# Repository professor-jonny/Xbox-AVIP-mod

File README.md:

# Xbox Avip mod

## Project Info
We all know that modern TV's are going away from component and composite video inputs in favor of newer technologies such as HDMI because of this there has been many people attempting various mods some great, some sketchy and some down right wrong.

This project started as I have seen a few people damage their Xbox consoles by attempting VGA and HDMI mods or made such a bad job of it that that I decided something needed to be done and I set out to make up a basic QSB to break out signals that you can use within the console to attached to external connectors or for use with an internal video adaptor solution.
Design goals were to be simple quick to install and have no complicated binary logic external switches to select the video modes.

The design also includes a buffer circuit to drive the internal h and v sync signals to 5v to give you proper VGA compliant signals with a suitable bios.

The system includes a PICAXE microcontroller to be able to switch video modes and other trickery, I designed it using this over a traditional microcontroller for ease of a user to modify using a three wire serial connection (in circuit) and partly from my lack of programming skills and time.
The PICAXE system enables any one to reprogram it without too much hassle and with minimal programming knowledge, both flow chart and basic programs are provided as samples that are easy to follow and understand.

I have also designed some breakout boards to join to the AVIP mod board, or you could use get IPEX/ U.FL to solder tails to connect to some sort of internal adaptor or converter in my perisomal Xbox I milled pads to place IPEX/ U.FL sockets on a component to HDMI adaptor.

I had double ended U.FL /IPEX Connectors made for this project officially the connectors are actually 50 ohm but were made with 75 ohm cable so the impedances are not perfect but it was the only aspect of the project I was not happy with, I planned to further update this project with a flex or FFC cable between boards but I'm unsure on impedance matching and the design of such a cable if someone can offer us some help with that I would be very grateful.

I realize at 720p the bandwidth can tip 75MHZ so the cable will need to be designed with microstrip or stripline transmission mitred bends or as such but I don't know much about the property's of these FFC cables or FlexPCB's or their connectors.

## Rational over other mods
I realize that there are other mods that offer better solutions or something of a similar goal such as native digital output or internal component to HDMI etc... but many are not simple or cost effective.
Many require de-soldering the original AVIP connector or micro soldering and for many people this is something that is beyond their skill set but a QSB solution is very noob friendly and hence my project.

## Features
The AVIP  mod has the following features:
  * Pluggable RF connectors for AV signals.
  * Impedance matched shielded analogue signals.
  * Automatic selection of backup AV mode.
  * VGA compliant 5V buffered V and H sync signals (non inverted).
  * Video mode toggling.
  * Fits all motherboard revisions.
  * Additional optional audio and video breakout boards.
  * Open source design.
  * In circuit user reprogrammable.
  * Audible/ light mode indication options.
  * Expansion capabilities.
  * AV pack boot fix (boot console without AV pack fitted).
  * Ability to still use original AV packs with this mod fitted.
  * Still works with Light Guns with a suitable TV and connection.
  * auto reconfigure of mode selection on reboot of console.

## Break out boards
I have managed to design some break out boards for the system my goal was to design them to be panel mounting on the back of the Xbox and look as if they were part of the system and not a hackjob.
I managed to find vertical components for the Break Out PCB's so I could mount the Break out board's Panel mount direct on the back of the Xbox with a spacer as opposed to a right angle mount PCB sockets so all that one would need is bolts and some nylon spacers and a Dremel tool to fit them.

you will notice that the component board provides every signal via RCA connectors to the back of the Xbox and it has a gap on either side where I would suggest you could place something else there like a 3.5mm vertical socket to power an external HDMI adaptor.

## Variants
I have modified the original v2 design with just some minor changes to do with the weird package format 2n2222a transistors I originally brought that I could not find again on aliexpress.
I have created two new V4 design's, one top mounted option for use with the Open XHD project (currently unfinished) and a new design with a greatly simplified sync buffer circuit, be aware that both these options currently are un tested and released "as is"

## Eagle library's
Along with v3 and v4 models I decided to create a proper library for the AVIP footprints and create an actual schematic as I did the v1 and 2 designs straight from a PCB layout with the footprint done with vias on the board, yes shocking I know but I feel much better now with the later designs that someone can mess with them with a lot less difficulty.

## Notes
I have made a proto type V1 board and have sold a few and can be considered tested but I have not made a v2 design the version 2 design just adds a few features an components but is basically unchanged from a design perspective.
list of Changes:
  * resistors on the serial data lines to force the PICAXE to start-up in RUN mode with out an external jumper.
  * Mode select current limiting resistors for the AV pack mode lines (thanks Psycho-Chewbacca for the tip here).
  * + and - terminal for programming outside of the console.
  * capacitor added to make PCB fit nicer on V1.6 consoles (bottom variant only).
  * added notch to clear the support on the bottom of the case (also spaced apart the RF connectors).
  * reset line to LPC port to reboot PICAXE on reboot of console.
  * upped resistor sizes to make hand soldering possible (I found this out the hard way)

## Future plans
I thought of combining an XIRC into this as the m2 does virtual multitasking and has a learning IR code library embedded and a small EPROM to store IR codes it would just need to be connected to stand by power and a handful of components to remote power on the Xbox from an IR remote control, but for the time being ill leave that up to you guys to modify looking forward to seeing a version 2 from someone :-) it will require voltage clamps for the mode select pins as the standby voltage is 3.3v but the mode pins are 5v.

the inclusion of a video Buffer to drive the external signals is not a bad idea as officially if you connect a AV pack and a external device you are driving two impedance match signals from the same output on the Xbox this was not really the intention of the project I only intend to use one output at a time.

# Links to software
This PCB design was done in eagle which is free to use and can be found here:

[Autodesk Eagle]( https://www.autodesk.com/products/eagle/free-download)

The PICAXE was programmed with the PICAXE editor 6 which can be found here:

[PICAXE Editor 6](https://picaxe.com/software/picaxe/picaxe-editor-6/)

The PCB design was converted to a sketch-up model by using the Eagleup script you can find information on the install and usage of it here:

[Eagleup ](https://eagleup.wordpress.com/installation-and-setup/)

The 3D model was done with SketchUp and a 30 day trial can be found here:

[SketchUp Trial](https://www.sketchup.com/try-sketchup)

You may use the free online version here:

[SketchUp Free](https://www.sketchup.com/plans-and-pricing/sketchup-free)

## Installation and programming Manual
You can find the latest version of the Installation and programming manual here it has additional info not available in this read me:

[AVIP mod Google Docs Manual](https://docs.google.com/document/d/1ht77iEsDnr8k5D_PiUR8pX0tqKVkKB9yM1Bdu0-4m4M/edit?usp=sharing)

## pictures
There is a few sample pictures located [here](https://github.com/professor-jonny/Xbox-AVIP-mod/tree/main/pictures) in the repo and a few extra below:

VGA break out board:

proto type v1:

proto type v3:

proto type v4:

proto type v4 top:

Wired to a component to HDMI adaptor:

## Licensing
This Project is free and open source.
  *  Hardware is shared under the [CERN OHL version 2.0.](https://ohwr.org/cernohl).
  *  The PICAXE program is shared under [GPLv3](https://www.gnu.org/licenses/quick-guide-gplv3.en.html).

If you like my work please consider a small donation to the XBMC4XBOX forum or one of the many Great Xbox resources out there you may also send me sample of clones of this project or buckets or cash or what ever :-)

For those interested there is also a bit of a build log [here on the XBMC4XBOX forum](https://www.xbmc4xbox.org.uk/forum/viewtopic.php?f=13&t=3644&hilit=xbox+avip+mod )

Id Like to Thank all that have helped to get it where it is today and a shutout to he crew over at XBMC4XBOX and a thanks to Psycho-Chewbacca (AKA benny Diamond) for his help.

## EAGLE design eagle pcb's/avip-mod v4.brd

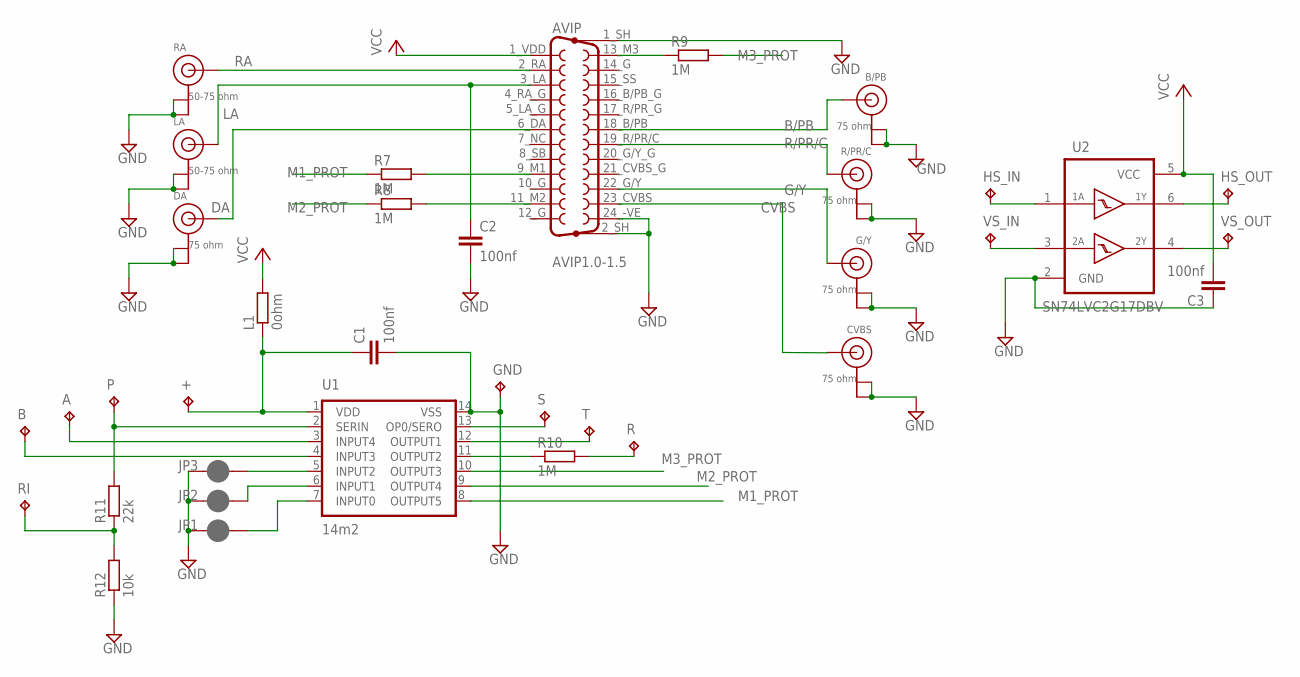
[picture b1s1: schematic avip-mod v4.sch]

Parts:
+: TPTP07SQ; TP07SQ
A: TPTP07SQ; TP07SQ
AVIP: AVIP1.0-1.5; AVIP-1.0-1.5
B: TPTP07SQ; TP07SQ
B/PB: 75 ohm; U.FL
C1, C2, C3: 100nf; C0603
CVBS: 75 ohm; U.FL
DA: 75 ohm; U.FL
G/Y: 75 ohm; U.FL
GND: TPTP07SQ; TP07SQ
HS_IN: TPTP07SQ; TP07SQ
HS_OUT: TPTP07SQ; TP07SQ
JP1, JP2, JP3: JUMPER-SMT_NO-SILK; SMT-JUMPER
L1: 0ohm; R0603
LA: 50-75 ohm; U.FL
P: TPTP07SQ; TP07SQ
R: TPTP07SQ; TP07SQ
R7, R8, R9, R10: 1M; R0603
R11: 22k; R0603
R12: 10k; R0603
R/PR/C: 75 ohm; U.FL
RA: 50-75 ohm; U.FL
RI: TPTP07SQ; TP07SQ
S: TPTP07SQ; TP07SQ
T: TPTP07SQ; TP07SQ
U1: 14m2; SO14
U2: SN74LVC2G17DBV; SOT23-6
VS_IN: TPTP07SQ; TP07SQ
VS_OUT: TPTP07SQ; TP07SQ

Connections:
A: A.TP, U1.3 (INPUT4)
B: B.TP, U1.4 (INPUT3)
B/PB: AVIP.18_B/PB, B/PB.3 (SIGNAL)
CVBS: AVIP.23_CVBS, CVBS.3 (SIGNAL)
DA: AVIP.6_DA, DA.3 (SIGNAL)
G/Y: AVIP.22_G/Y, G/Y.3 (SIGNAL)
GND: AVIP.1_SH, AVIP.2_SH, AVIP.24_-VE (25_VSS), B/PB.1 (GND), B/PB.2 (GND), C1.2, C2.2, C3.1, CVBS.1 (GND), CVBS.2 (GND), DA.1 (GND), DA.2 (GND), G/Y.1 (GND), G/Y.2 (GND), GND.TP, JP1.1, JP2.1, JP3.1, LA.1 (GND), LA.2 (GND), R12.1, R/PR/C.1 (GND), R/PR/C.2 (GND), RA.1 (GND), RA.2 (GND), U1.14 (VSS), U2.2 (GND)
H_SYNC_IN: HS_IN.TP, U2.1 (1A)
H_SYNC_OUT: HS_OUT.TP, U2.6 (1Y)
LA: AVIP.3_LA, C2.1, LA.3 (SIGNAL)
M1: AVIP.9_M1, R7.2
M1S: JP1.2, U1.7 (INPUT0)
M1_PROT: R7.1, U1.8 (OUTPUT5)
M2: AVIP.11_M2, R8.2
M2S: JP2.2, U1.6 (INPUT1)
M2_PROT: R8.1, U1.9 (OUTPUT4)
M3: AVIP.13_M3, R9.1
M3S: JP3.2, U1.5 (INPUT2)
M3_PROT: R9.2, U1.10 (OUTPUT3)
PROG: P.TP, R11.2, U1.2 (SERIN)
R/PR/C: AVIP.19_R/PR/C, R/PR/C.3 (SIGNAL)
RA: AVIP.2_RA, RA.3 (SIGNAL)
RESET: R.TP, R10.2
RESET_PROT: R10.1, U1.11 (OUTPUT2)
RING: R11.1, R12.2, RI.TP
SPEAK: S.TP, U1.13 (OP0/SERO)
TOGGLE: T.TP, U1.12 (OUTPUT1)
VCC: AVIP.1_VDD, C3.2, L1.2, U2.5 (VCC)
VDD: +.TP, C1.1, L1.1, U1.1 (VDD)
V_SYNC_IN: U2.3 (2A), VS_IN.TP
V_SYNC_OUT: U2.4 (2Y), VS_OUT.TP

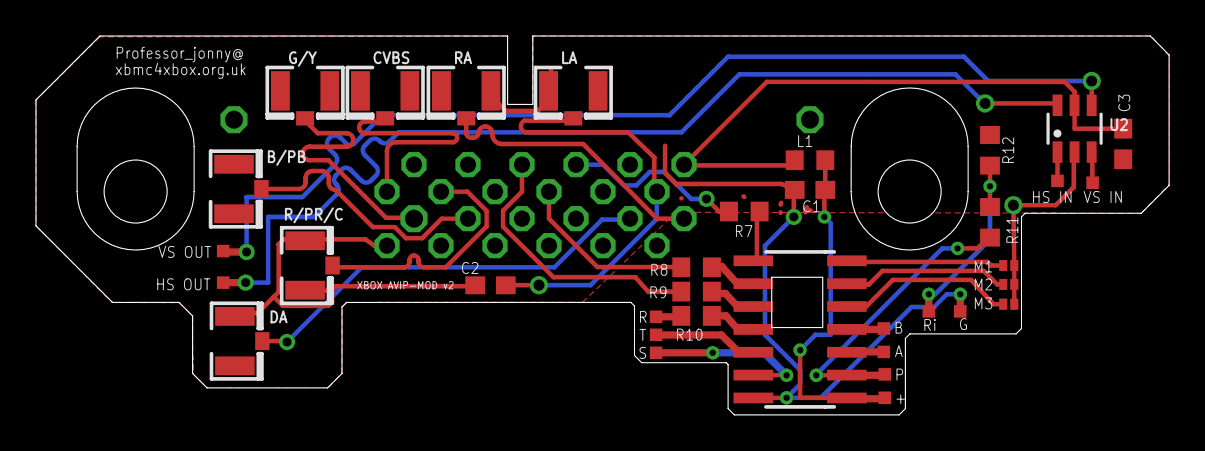
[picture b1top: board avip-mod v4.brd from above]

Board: 2 copper layers, 63.0 x 21.1 mm, 36 parts (1 on the bottom side), 31 nets.

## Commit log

2022-11-12 Initial commit
    Add README.md
    Init import of AVIP mod project.
2024-02-13 schematic sync and new PCB layout and footprint
    update the project and sync the schematic to the pcb with new lib for the AVIP connector.
    AVIP was done before in pads and vias fixed it up properly with a valid footprint
    Replaced the transistors with 2n2222 could not source the original ones and have been discontinued (note new layout for transistors to suit.)
    Fixed up a few DRC rules and made solder mask cover vias.
2024-02-15 Update project
    Add Chihiro and 1.6 console footprints to AVIP library.
    Add alternative v4 Schmitt Trigger buffer circuit saves plenty of space on the PCB will come in handy with top design PCB in future.
    Update libs and PCB
    Add jumper pads instead of 0 ohm resistors to save space.
    optimize PCB layout and fix DRC errors
2024-02-16 Updates
    Combined non stock items into single lib.
    update pcb, clean up some more DRC issues.
    reroute some traces to simplify design.
2024-02-16 create new top motherboard variant
    Create new top motherboard variant for use with Open-XHD project.
    updated library with more Xbox AVIP footprints with removed shields.
    updated read me.
2024-02-18 Fix PCB preview and update pictures
    Conflict between mill and dimensions layer causing all PCB's to not show up in manufacture preview.
    Add pictures of v3, v4 and v4 top PCB.
2024-02-18 crop pictures
